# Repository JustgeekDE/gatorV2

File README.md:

# Gator
Gator started as a small project to built a set of multipurpose, breadboard friendly TTL gates. It has since morphed into the endeavour to create a complete CPU built out of only discrete NPN transistors, resistors and capacitors.  
It also serves as a test bed for a few techniques to improve the hardware development process.

(Above is a 1-bit full adder)

## Errata
- The current instruction set is missing any way to read a memory address from a register. This makes pointers, array iterations and linked list impossible or at least very hard.

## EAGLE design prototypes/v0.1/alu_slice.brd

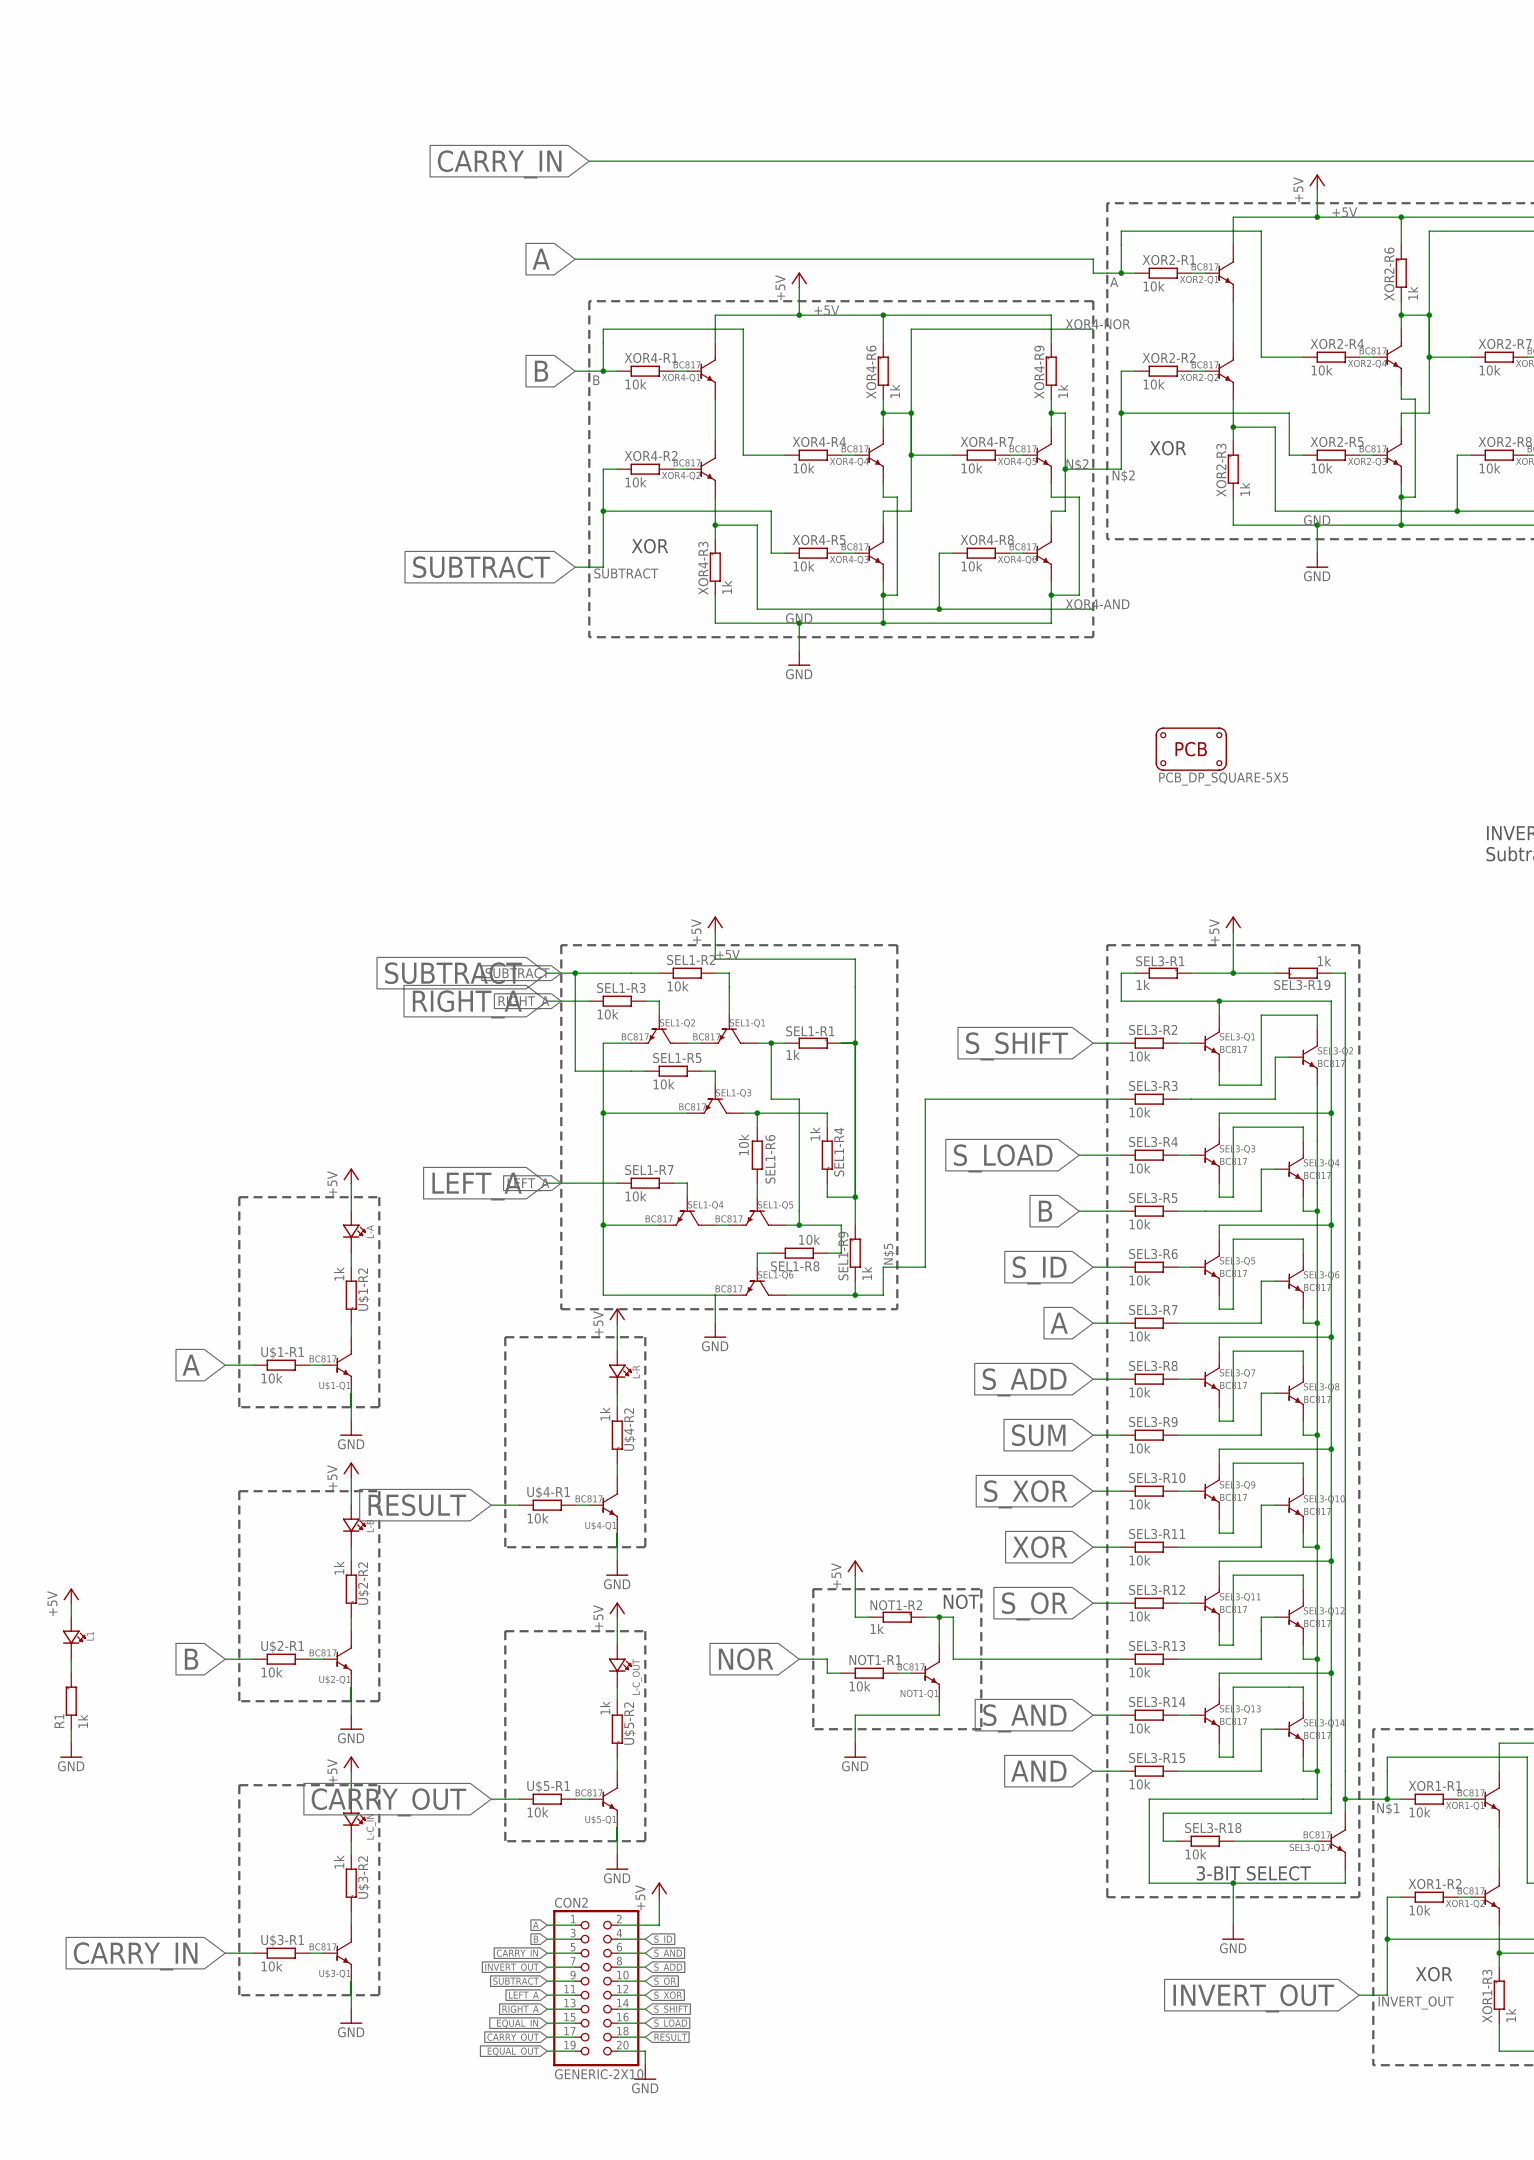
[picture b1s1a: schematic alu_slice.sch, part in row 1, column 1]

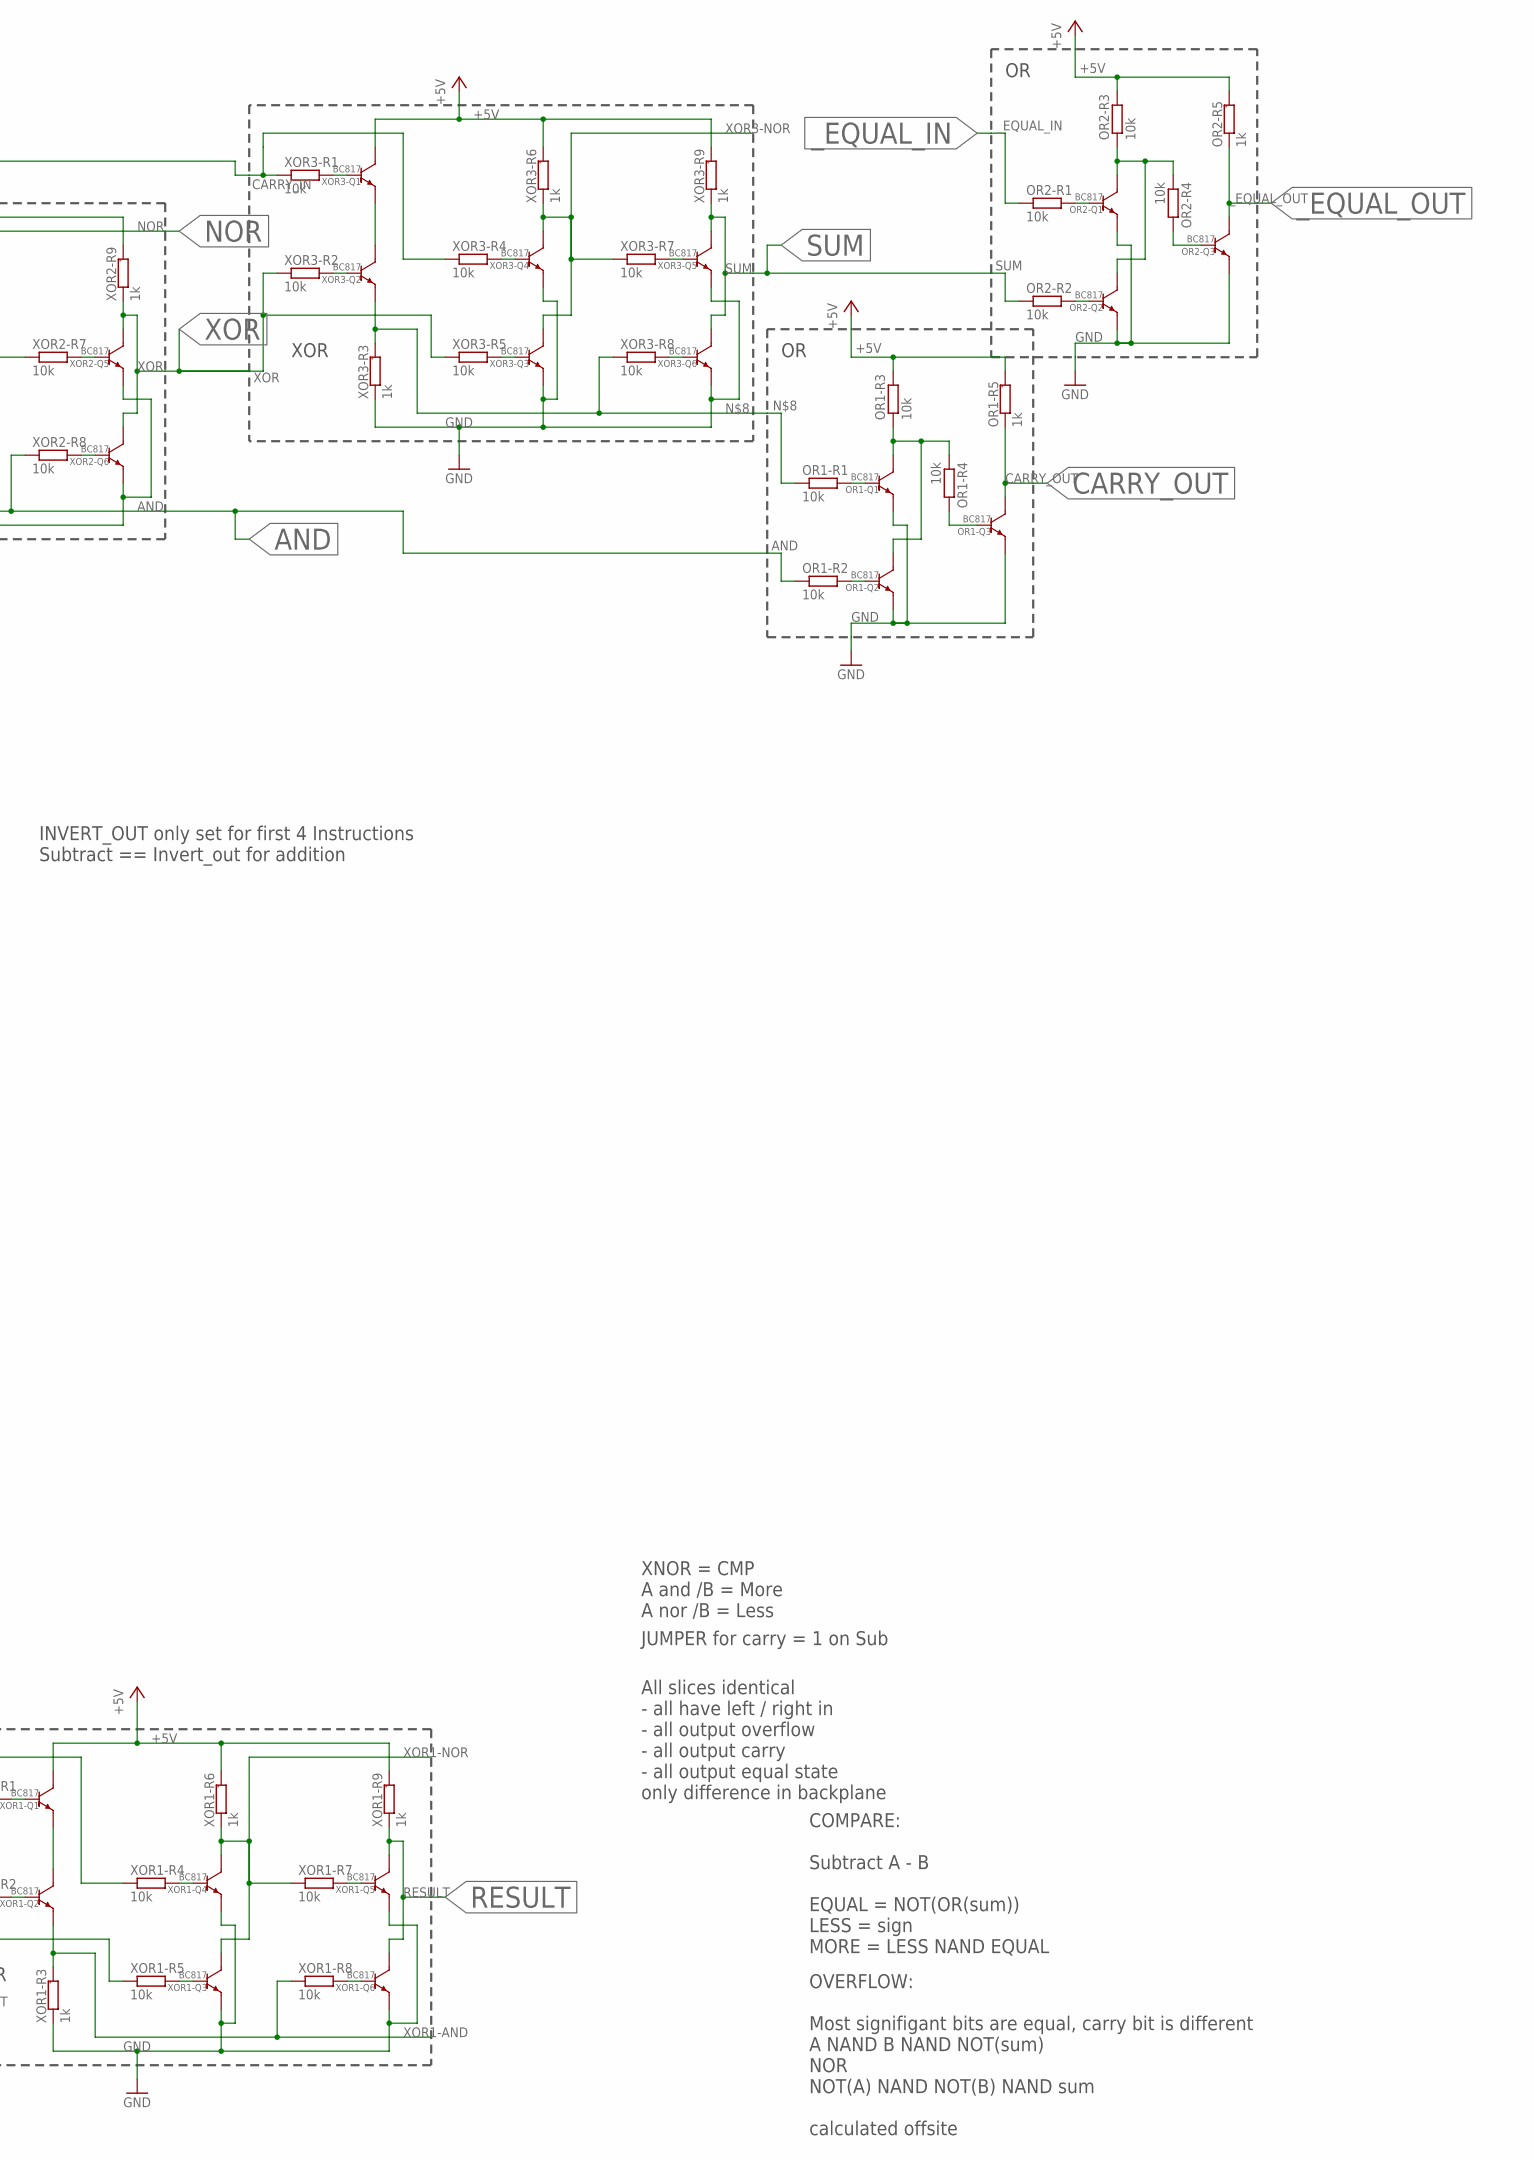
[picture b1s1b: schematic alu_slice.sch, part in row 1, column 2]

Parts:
CON2: GENERIC-2X10; PINHEADER-100MIL-2X10-EDGE
L1: LED0805; CHIPLED_0805
L-A: LED0603; CHIPLED_0603
L-B: LED0603; CHIPLED_0603
L-C_IN: LED0603; CHIPLED_0603
L-C_OUT: LED0603; CHIPLED_0603
L-R: LED0603; CHIPLED_0603
NOT1-Q1: BC817; SOT23
NOT1-R1: 10k; R0603
NOT1-R2: 1k; R0603-MARK
OR1-Q1, OR1-Q2, OR1-Q3, OR2-Q1, OR2-Q2, OR2-Q3: BC817; SOT23
OR1-R1, OR1-R2, OR1-R3, OR1-R4, OR2-R1, OR2-R2, OR2-R3, OR2-R4: 10k; R0603
OR1-R5, OR2-R5: 1k; R0603-MARK
PCB1: PCB_DP_SQUARE-5X5; DP5050_V1
R1: 1k; R0603-MARK
SEL1-Q1, SEL1-Q2, SEL1-Q3, SEL1-Q4, SEL1-Q5, SEL1-Q6, SEL3-Q1, SEL3-Q2, SEL3-Q3, SEL3-Q4, SEL3-Q5, SEL3-Q6, SEL3-Q7, SEL3-Q8, SEL3-Q9, SEL3-Q10, SEL3-Q11, SEL3-Q12, SEL3-Q13, SEL3-Q14, SEL3-Q17: BC817; SOT23
SEL1-R1, SEL1-R4, SEL1-R9, SEL3-R1, SEL3-R19: 1k; R0603-MARK
SEL1-R2, SEL1-R3, SEL1-R5, SEL1-R6, SEL1-R7, SEL1-R8, SEL3-R2, SEL3-R3, SEL3-R4, SEL3-R5, SEL3-R6, SEL3-R7, SEL3-R8, SEL3-R9, SEL3-R10, SEL3-R11, SEL3-R12, SEL3-R13, SEL3-R14, SEL3-R15, SEL3-R18: 10k; R0603
U$1-Q1, U$2-Q1, U$3-Q1, U$4-Q1, U$5-Q1: BC817; SOT23
U$1-R1, U$2-R1, U$3-R1, U$4-R1, U$5-R1: 10k; R0603
U$1-R2, U$2-R2, U$3-R2, U$4-R2, U$5-R2: 1k; R0603-MARK
XOR1-Q1, XOR1-Q2, XOR1-Q3, XOR1-Q4, XOR1-Q5, XOR1-Q6, XOR2-Q1, XOR2-Q2, XOR2-Q3, XOR2-Q4, XOR2-Q5, XOR2-Q6, XOR3-Q1, XOR3-Q2, XOR3-Q3, XOR3-Q4, XOR3-Q5, XOR3-Q6, XOR4-Q1, XOR4-Q2, XOR4-Q3, XOR4-Q4, XOR4-Q5, XOR4-Q6: BC817; SOT23
XOR1-R1, XOR1-R2, XOR1-R4, XOR1-R5, XOR1-R7, XOR1-R8, XOR2-R1, XOR2-R2, XOR2-R4, XOR2-R5, XOR2-R7, XOR2-R8, XOR3-R1, XOR3-R2, XOR3-R4, XOR3-R5, XOR3-R7, XOR3-R8, XOR4-R1, XOR4-R2, XOR4-R4, XOR4-R5, XOR4-R7, XOR4-R8: 10k; R0603
XOR1-R3, XOR1-R6, XOR1-R9, XOR2-R3, XOR2-R6, XOR2-R9, XOR3-R3, XOR3-R6, XOR3-R9, XOR4-R3, XOR4-R6, XOR4-R9: 1k; R0603-MARK

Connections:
+5V: CON2.2, L1.A, L-A.A, L-B.A, L-C_IN.A, L-C_OUT.A, L-R.A, NOT1-R2.1, OR1-R3.2, OR1-R5.2, OR2-R3.2, OR2-R5.2, SEL1-R1.2, SEL1-R4.2, SEL1-R9.2, SEL3-R1.2, SEL3-R19.2, XOR1-Q1.P$3 (COLLECTOR), XOR1-R6.2, XOR1-R9.2, XOR2-Q1.P$3 (COLLECTOR), XOR2-R6.2, XOR2-R9.2, XOR3-Q1.P$3 (COLLECTOR), XOR3-R6.2, XOR3-R9.2, XOR4-Q1.P$3 (COLLECTOR), XOR4-R6.2, XOR4-R9.2
A: CON2.1, SEL3-R7.1, U$1-R1.1, XOR2-R1.1, XOR2-R4.1
AND: OR1-R2.1, SEL3-R15.1, XOR2-Q2.P$2 (EMITTER), XOR2-R3.2, XOR2-R8.1
B: CON2.3, SEL3-R5.1, U$2-R1.1, XOR4-R1.1, XOR4-R4.1
CARRY_IN: CON2.5, U$3-R1.1, XOR3-R1.1, XOR3-R4.1
CARRY_OUT: CON2.17, OR1-Q3.P$3 (COLLECTOR), OR1-R5.1, U$5-R1.1
GND: CON2.20, NOT1-Q1.P$2 (EMITTER), OR1-Q1.P$2 (EMITTER), OR1-Q2.P$2 (EMITTER), OR1-Q3.P$2 (EMITTER), OR2-Q1.P$2 (EMITTER), OR2-Q2.P$2 (EMITTER), OR2-Q3.P$2 (EMITTER), R1.1, SEL1-Q2.P$2 (EMITTER), SEL1-Q3.P$2 (EMITTER), SEL1-Q4.P$2 (EMITTER), SEL1-Q6.P$2 (EMITTER), SEL3-Q2.P$2 (EMITTER), SEL3-Q4.P$2 (EMITTER), SEL3-Q6.P$2 (EMITTER), SEL3-Q8.P$2 (EMITTER), SEL3-Q10.P$2 (EMITTER), SEL3-Q12.P$2 (EMITTER), SEL3-Q14.P$2 (EMITTER), SEL3-Q17.P$2 (EMITTER), U$1-Q1.P$2 (EMITTER), U$2-Q1.P$2 (EMITTER), U$3-Q1.P$2 (EMITTER), U$4-Q1.P$2 (EMITTER), U$5-Q1.P$2 (EMITTER), XOR1-Q3.P$2 (EMITTER), XOR1-Q4.P$2 (EMITTER), XOR1-Q5.P$2 (EMITTER), XOR1-Q6.P$2 (EMITTER), XOR1-R3.1, XOR2-Q3.P$2 (EMITTER), XOR2-Q4.P$2 (EMITTER), XOR2-Q5.P$2 (EMITTER), XOR2-Q6.P$2 (EMITTER), XOR2-R3.1, XOR3-Q3.P$2 (EMITTER), XOR3-Q4.P$2 (EMITTER), XOR3-Q5.P$2 (EMITTER), XOR3-Q6.P$2 (EMITTER), XOR3-R3.1, XOR4-Q3.P$2 (EMITTER), XOR4-Q4.P$2 (EMITTER), XOR4-Q5.P$2 (EMITTER), XOR4-Q6.P$2 (EMITTER), XOR4-R3.1
INVERT_OUT: CON2.7, XOR1-R2.1, XOR1-R5.1
LEFT_A: CON2.11, SEL1-R7.1
unnamed: SEL3-Q17.P$3 (COLLECTOR), SEL3-R19.1, XOR1-R1.1, XOR1-R4.1
unnamed: XOR2-R2.1, XOR2-R5.1, XOR4-Q5.P$3 (COLLECTOR), XOR4-Q6.P$3 (COLLECTOR), XOR4-R9.1
unnamed: NOT1-Q1.P$3 (COLLECTOR), NOT1-R2.2, SEL3-R13.1
unnamed: SEL1-Q6.P$3 (COLLECTOR), SEL1-R9.1, SEL3-R3.1
unnamed: L1.C, R1.2
unnamed: OR1-R1.1, XOR3-Q2.P$2 (EMITTER), XOR3-R3.2, XOR3-R8.1
NOR: NOT1-R1.1, XOR2-Q3.P$3 (COLLECTOR), XOR2-Q4.P$3 (COLLECTOR), XOR2-R6.1, XOR2-R7.1
NOT1-N$14: NOT1-Q1.P$1 (BASE), NOT1-R1.2
OR1-N$7: OR1-Q1.P$1 (BASE), OR1-R1.2
OR1-N$9: OR1-Q2.P$1 (BASE), OR1-R2.2
OR1-N$10: OR1-Q3.P$1 (BASE), OR1-R4.2
OR1-N$11: OR1-Q1.P$3 (COLLECTOR), OR1-Q2.P$3 (COLLECTOR), OR1-R3.1, OR1-R4.1
OR2-N$7: OR2-Q1.P$1 (BASE), OR2-R1.2
OR2-N$9: OR2-Q2.P$1 (BASE), OR2-R2.2
OR2-N$10: OR2-Q3.P$1 (BASE), OR2-R4.2
OR2-N$11: OR2-Q1.P$3 (COLLECTOR), OR2-Q2.P$3 (COLLECTOR), OR2-R3.1, OR2-R4.1
RESULT: CON2.18, U$4-R1.1, XOR1-Q5.P$3 (COLLECTOR), XOR1-Q6.P$3 (COLLECTOR), XOR1-R9.1
RIGHT_A: CON2.13, SEL1-R3.1
SEL1-I-S2: SEL1-Q3.P$3 (COLLECTOR), SEL1-R4.1, SEL1-R6.1
SEL1-N$53: SEL1-Q1.P$1 (BASE), SEL1-R2.2
SEL1-N$55: SEL1-Q2.P$1 (BASE), SEL1-R3.2
SEL1-N$56: SEL1-Q1.P$2 (EMITTER), SEL1-Q2.P$3 (COLLECTOR)
SEL1-N$57: SEL1-Q5.P$1 (BASE), SEL1-R6.2
SEL1-N$58: SEL1-Q4.P$1 (BASE), SEL1-R7.2
SEL1-N$59: SEL1-Q4.P$3 (COLLECTOR), SEL1-Q5.P$2 (EMITTER)
SEL1-N$60: SEL1-Q6.P$1 (BASE), SEL1-R8.2
SEL1-N$62: SEL1-Q3.P$1 (BASE), SEL1-R5.2
SEL1-SEL_INT1: SEL1-Q1.P$3 (COLLECTOR), SEL1-Q5.P$3 (COLLECTOR), SEL1-R1.1, SEL1-R8.1
SEL3-N$27: SEL3-Q1.P$1 (BASE), SEL3-R2.2
SEL3-N$28: SEL3-Q2.P$1 (BASE), SEL3-R3.2
SEL3-N$29: SEL3-Q1.P$2 (EMITTER), SEL3-Q2.P$3 (COLLECTOR)
SEL3-N$32: SEL3-Q3.P$1 (BASE), SEL3-R4.2
SEL3-N$33: SEL3-Q4.P$1 (BASE), SEL3-R5.2
SEL3-N$34: SEL3-Q3.P$2 (EMITTER), SEL3-Q4.P$3 (COLLECTOR)
SEL3-N$35: SEL3-Q5.P$1 (BASE), SEL3-R6.2
SEL3-N$36: SEL3-Q6.P$1 (BASE), SEL3-R7.2
SEL3-N$37: SEL3-Q5.P$2 (EMITTER), SEL3-Q6.P$3 (COLLECTOR)
SEL3-N$38: SEL3-Q7.P$1 (BASE), SEL3-R8.2
SEL3-N$39: SEL3-Q8.P$1 (BASE), SEL3-R9.2
SEL3-N$40: SEL3-Q7.P$2 (EMITTER), SEL3-Q8.P$3 (COLLECTOR)
SEL3-N$41: SEL3-Q9.P$1 (BASE), SEL3-R10.2
SEL3-N$42: SEL3-Q10.P$1 (BASE), SEL3-R11.2
SEL3-N$43: SEL3-Q9.P$2 (EMITTER), SEL3-Q10.P$3 (COLLECTOR)
SEL3-N$44: SEL3-Q11.P$1 (BASE), SEL3-R12.2
SEL3-N$45: SEL3-Q12.P$1 (BASE), SEL3-R13.2
SEL3-N$46: SEL3-Q11.P$2 (EMITTER), SEL3-Q12.P$3 (COLLECTOR)
SEL3-N$47: SEL3-Q13.P$1 (BASE), SEL3-R14.2
SEL3-N$48: SEL3-Q14.P$1 (BASE), SEL3-R15.2
SEL3-N$49: SEL3-Q13.P$2 (EMITTER), SEL3-Q14.P$3 (COLLECTOR)
SEL3-N$54: SEL3-Q17.P$1 (BASE), SEL3-R18.2
SEL3-SEL_INT: SEL3-Q1.P$3 (COLLECTOR), SEL3-Q3.P$3 (COLLECTOR), SEL3-Q5.P$3 (COLLECTOR), SEL3-Q7.P$3 (COLLECTOR), SEL3-Q9.P$3 (COLLECTOR), SEL3-Q11.P$3 (COLLECTOR), SEL3-Q13.P$3 (COLLECTOR), SEL3-R1.1, SEL3-R18.1
SUBTRACT: CON2.9, SEL1-R2.1, SEL1-R5.1, XOR4-R2.1, XOR4-R5.1
SUM: OR2-R2.1, SEL3-R9.1, XOR3-Q5.P$3 (COLLECTOR), XOR3-Q6.P$3 (COLLECTOR), XOR3-R9.1
S_ADD: CON2.8, SEL3-R8.1
S_AND: CON2.6, SEL3-R14.1
S_ID: CON2.4, SEL3-R6.1
S_LOAD: CON2.16, SEL3-R4.1
S_OR: CON2.10, SEL3-R12.1
S_SHIFT: CON2.14, SEL3-R2.1
S_XOR: CON2.12, SEL3-R10.1
U$1-INT: L-A.C, U$1-R2.1
U$1-N$1: U$1-Q1.P$3 (COLLECTOR), U$1-R2.2
U$1-N$16: U$1-Q1.P$1 (BASE), U$1-R1.2
U$2-INT: L-B.C, U$2-R2.1
U$2-N$1: U$2-Q1.P$3 (COLLECTOR), U$2-R2.2
U$2-N$16: U$2-Q1.P$1 (BASE), U$2-R1.2
U$3-INT: L-C_IN.C, U$3-R2.1
U$3-N$1: U$3-Q1.P$3 (COLLECTOR), U$3-R2.2
U$3-N$16: U$3-Q1.P$1 (BASE), U$3-R1.2
U$4-INT: L-R.C, U$4-R2.1
U$4-N$1: U$4-Q1.P$3 (COLLECTOR), U$4-R2.2
U$4-N$16: U$4-Q1.P$1 (BASE), U$4-R1.2
U$5-INT: L-C_OUT.C, U$5-R2.1
U$5-N$1: U$5-Q1.P$3 (COLLECTOR), U$5-R2.2
U$5-N$16: U$5-Q1.P$1 (BASE), U$5-R1.2
XOR: SEL3-R11.1, XOR2-Q5.P$3 (COLLECTOR), XOR2-Q6.P$3 (COLLECTOR), XOR2-R9.1, XOR3-R2.1, XOR3-R5.1
XOR1-AND: XOR1-Q2.P$2 (EMITTER), XOR1-R3.2, XOR1-R8.1
XOR1-N$19: XOR1-Q1.P$2 (EMITTER), XOR1-Q2.P$3 (COLLECTOR)
XOR1-N$21: XOR1-Q1.P$1 (BASE), XOR1-R1.2
XOR1-N$22: XOR1-Q2.P$1 (BASE), XOR1-R2.2
XOR1-N$23: XOR1-Q3.P$1 (BASE), XOR1-R5.2
XOR1-N$24: XOR1-Q4.P$1 (BASE), XOR1-R4.2
XOR1-N$25: XOR1-Q6.P$1 (BASE), XOR1-R8.2
XOR1-N$26: XOR1-Q5.P$1 (BASE), XOR1-R7.2
XOR1-NOR: XOR1-Q3.P$3 (COLLECTOR), XOR1-Q4.P$3 (COLLECTOR), XOR1-R6.1, XOR1-R7.1
XOR2-N$19: XOR2-Q1.P$2 (EMITTER), XOR2-Q2.P$3 (COLLECTOR)
XOR2-N$21: XOR2-Q1.P$1 (BASE), XOR2-R1.2
XOR2-N$22: XOR2-Q2.P$1 (BASE), XOR2-R2.2
XOR2-N$23: XOR2-Q3.P$1 (BASE), XOR2-R5.2
XOR2-N$24: XOR2-Q4.P$1 (BASE), XOR2-R4.2
XOR2-N$25: XOR2-Q6.P$1 (BASE), XOR2-R8.2
XOR2-N$26: XOR2-Q5.P$1 (BASE), XOR2-R7.2
XOR3-N$19: XOR3-Q1.P$2 (EMITTER), XOR3-Q2.P$3 (COLLECTOR)
XOR3-N$21: XOR3-Q1.P$1 (BASE), XOR3-R1.2
XOR3-N$22: XOR3-Q2.P$1 (BASE), XOR3-R2.2
XOR3-N$23: XOR3-Q3.P$1 (BASE), XOR3-R5.2
XOR3-N$24: XOR3-Q4.P$1 (BASE), XOR3-R4.2
XOR3-N$25: XOR3-Q6.P$1 (BASE), XOR3-R8.2
XOR3-N$26: XOR3-Q5.P$1 (BASE), XOR3-R7.2
XOR3-NOR: XOR3-Q3.P$3 (COLLECTOR), XOR3-Q4.P$3 (COLLECTOR), XOR3-R6.1, XOR3-R7.1
XOR4-AND: XOR4-Q2.P$2 (EMITTER), XOR4-R3.2, XOR4-R8.1
XOR4-N$19: XOR4-Q1.P$2 (EMITTER), XOR4-Q2.P$3 (COLLECTOR)
XOR4-N$21: XOR4-Q1.P$1 (BASE), XOR4-R1.2
XOR4-N$22: XOR4-Q2.P$1 (BASE), XOR4-R2.2
XOR4-N$23: XOR4-Q3.P$1 (BASE), XOR4-R5.2
XOR4-N$24: XOR4-Q4.P$1 (BASE), XOR4-R4.2
XOR4-N$25: XOR4-Q6.P$1 (BASE), XOR4-R8.2
XOR4-N$26: XOR4-Q5.P$1 (BASE), XOR4-R7.2
XOR4-NOR: XOR4-Q3.P$3 (COLLECTOR), XOR4-Q4.P$3 (COLLECTOR), XOR4-R6.1, XOR4-R7.1
_EQUAL_IN: CON2.15, OR2-R1.1
_EQUAL_OUT: CON2.19, OR2-Q3.P$3 (COLLECTOR), OR2-R5.1

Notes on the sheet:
XNOR = CMP
A and /B = More A nor /B = Less
JUMPER for carry = 1 on Sub
All slices identical - all have left / right in - all output overflow - all output carry - all output equal state only difference in backplane
COMPARE: Subtract A - B EQUAL = NOT(OR(sum)) LESS = sign MORE = LESS NAND EQUAL
OVERFLOW: Most signifigant bits are equal, carry bit is different A NAND B NAND NOT(sum) NOR NOT(A) NAND NOT(B) NAND sum calculated offsite
INVERT_OUT only set for first 4 Instructions Subtract == Invert_out for addition
3-BIT SELECT
NOT
XOR

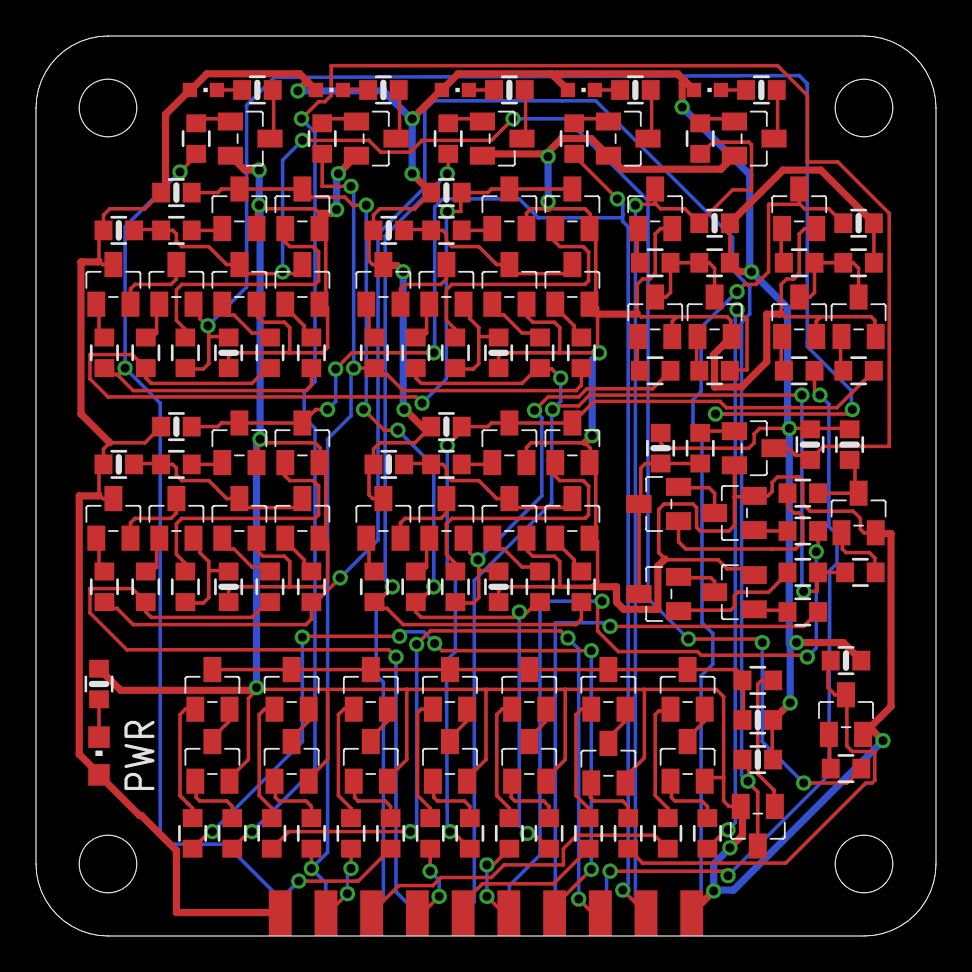
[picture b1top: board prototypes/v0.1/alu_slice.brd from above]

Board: 2 copper layers, 50.0 x 50.0 mm, 151 parts (1 on the bottom side), 120 nets.

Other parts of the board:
U$1: LOGO-JUSTGEEK-XS

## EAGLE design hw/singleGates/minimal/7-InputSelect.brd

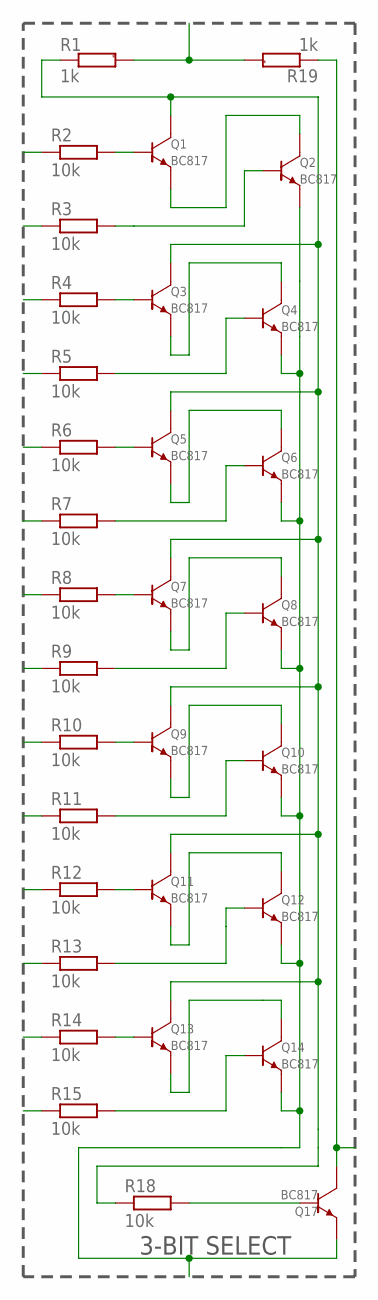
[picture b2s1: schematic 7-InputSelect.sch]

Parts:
Q1, Q2, Q3, Q4, Q5, Q6, Q7, Q8, Q9, Q10, Q11, Q12, Q13, Q14, Q17: BC817; SOT23
R1, R19: 1k; R0603-MARK
R2, R3, R4, R5, R6, R7, R8, R9, R10, R11, R12, R13, R14, R15, R18: 10k; R0603

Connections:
I1: R3.1
I2: R5.1
I3: R7.1
I4: R9.1
I5: R11.1
I6: R13.1
I7: R15.1
unnamed: Q1.P$1 (BASE), R2.2
unnamed: Q2.P$1 (BASE), R3.2
unnamed: Q1.P$2 (EMITTER), Q2.P$3 (COLLECTOR)
unnamed: Q3.P$1 (BASE), R4.2
unnamed: Q4.P$1 (BASE), R5.2
unnamed: Q3.P$2 (EMITTER), Q4.P$3 (COLLECTOR)
unnamed: Q5.P$1 (BASE), R6.2
unnamed: Q6.P$1 (BASE), R7.2
unnamed: Q5.P$2 (EMITTER), Q6.P$3 (COLLECTOR)
unnamed: Q7.P$1 (BASE), R8.2
unnamed: Q8.P$1 (BASE), R9.2
unnamed: Q7.P$2 (EMITTER), Q8.P$3 (COLLECTOR)
unnamed: Q9.P$1 (BASE), R10.2
unnamed: Q10.P$1 (BASE), R11.2
unnamed: Q9.P$2 (EMITTER), Q10.P$3 (COLLECTOR)
unnamed: Q11.P$1 (BASE), R12.2
unnamed: Q12.P$1 (BASE), R13.2
unnamed: Q11.P$2 (EMITTER), Q12.P$3 (COLLECTOR)
unnamed: Q13.P$1 (BASE), R14.2
unnamed: Q14.P$1 (BASE), R15.2
unnamed: Q13.P$2 (EMITTER), Q14.P$3 (COLLECTOR)
unnamed: Q17.P$1 (BASE), R18.2
OUT: Q17.P$3 (COLLECTOR), R19.1
S1: R2.1
S2: R4.1
S3: R6.1
S4: R8.1
S5: R10.1
S6: R12.1
S7: R14.1
SEL_INT: Q1.P$3 (COLLECTOR), Q3.P$3 (COLLECTOR), Q5.P$3 (COLLECTOR), Q7.P$3 (COLLECTOR), Q9.P$3 (COLLECTOR), Q11.P$3 (COLLECTOR), Q13.P$3 (COLLECTOR), R1.1, R18.1
_VN: Q2.P$2 (EMITTER), Q4.P$2 (EMITTER), Q6.P$2 (EMITTER), Q8.P$2 (EMITTER), Q10.P$2 (EMITTER), Q12.P$2 (EMITTER), Q14.P$2 (EMITTER), Q17.P$2 (EMITTER)
_VP: R1.2, R19.2

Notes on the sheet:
3-BIT SELECT

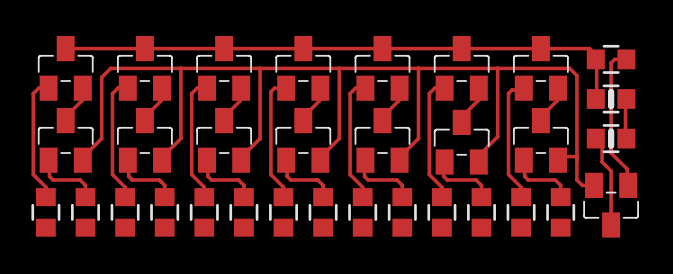
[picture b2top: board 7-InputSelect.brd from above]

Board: 2 copper layers, 32 parts (0 on the bottom side), 26 nets.

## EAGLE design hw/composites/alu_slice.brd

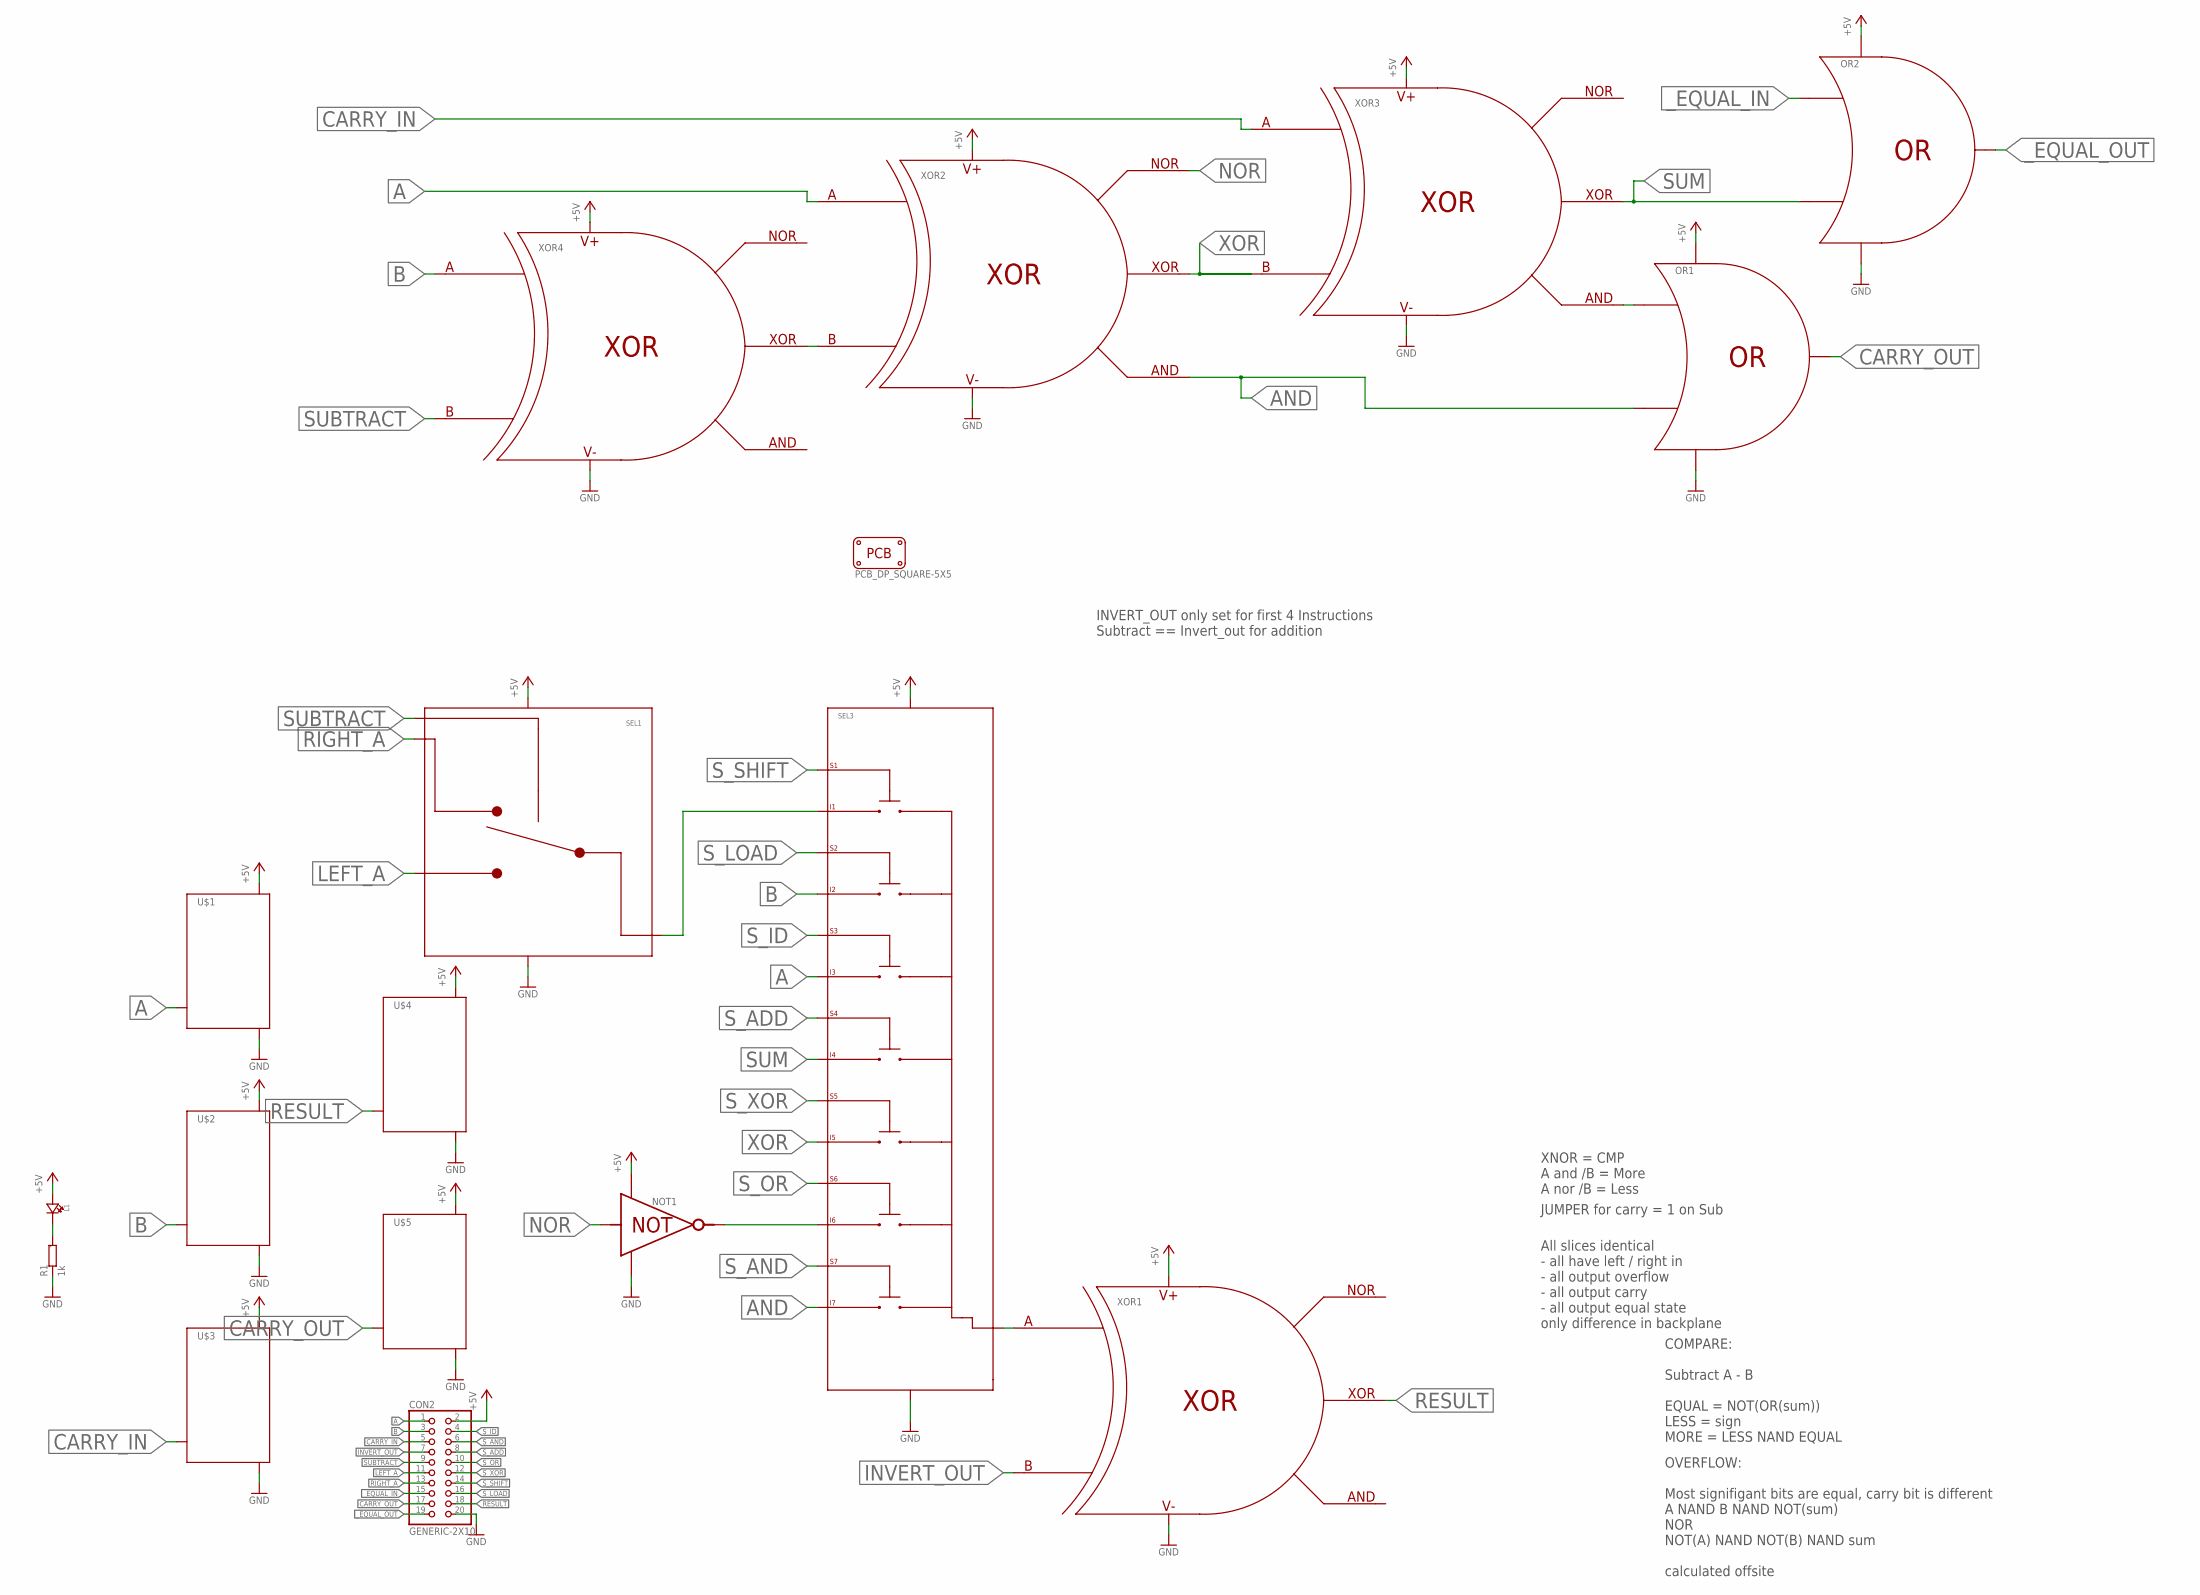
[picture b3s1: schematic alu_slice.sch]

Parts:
CON2: GENERIC-2X10; PINHEADER-100MIL-2X10-EDGE
L1: LED0805; CHIPLED_0805
NOT1: NOTVERTICAL; NOT-VERTICAL
OR1, OR2: OR
PCB1: PCB_DP_SQUARE-5X5; DP5050_V1
R1: 1k; R0603-MARK
SEL1: 1_BIT_SELECT; SELECTOR-2-LANE-NOMUX
SEL3: 7_VAL_SELECT; SELECTOR-7_BIT-NOMUX
U$1, U$2, U$3, U$4, U$5: LEDDRIVER
XOR1, XOR2, XOR3, XOR4: XOR

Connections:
+5V: CON2.2, L1.A, NOT1._VP, OR1._VP, OR2._VP, SEL1._VP, SEL3._VP, U$1._VP, U$2._VP, U$3._VP, U$4._VP, U$5._VP, XOR1._VP, XOR2._VP, XOR3._VP, XOR4._VP
A: CON2.1, SEL3.I3, U$1.A, XOR2.A
AND: OR1.B, SEL3.I7, XOR2.AND
B: CON2.3, SEL3.I2, U$2.A, XOR4.A
CARRY_IN: CON2.5, U$3.A, XOR3.A
CARRY_OUT: CON2.17, OR1.OR, U$5.A
GND: CON2.20, NOT1._VN, OR1._VN, OR2._VN, R1.1, SEL1._VN, SEL3._VN, U$1._VN, U$2._VN, U$3._VN, U$4._VN, U$5._VN, XOR1._VN, XOR2._VN, XOR3._VN, XOR4._VN
INVERT_OUT: CON2.7, XOR1.B
LEFT_A: CON2.11, SEL1.B
unnamed: SEL3.OUT, XOR1.A
unnamed: XOR2.B, XOR4.XOR
unnamed: NOT1.NOT, SEL3.I6
unnamed: SEL1.OUT, SEL3.I1
unnamed: L1.C, R1.2
unnamed: OR1.A, XOR3.AND
NOR: NOT1.A, XOR2.NOR
RESULT: CON2.18, U$4.A, XOR1.XOR
RIGHT_A: CON2.13, SEL1.A
SUBTRACT: CON2.9, SEL1.SEL, XOR4.B
SUM: OR2.B, SEL3.I4, XOR3.XOR
S_ADD: CON2.8, SEL3.S4
S_AND: CON2.6, SEL3.S7
S_ID: CON2.4, SEL3.S3
S_LOAD: CON2.16, SEL3.S2
S_OR: CON2.10, SEL3.S6
S_SHIFT: CON2.14, SEL3.S1
S_XOR: CON2.12, SEL3.S5
XOR: SEL3.I5, XOR2.XOR, XOR3.B
_EQUAL_IN: CON2.15, OR2.A
_EQUAL_OUT: CON2.19, OR2.OR

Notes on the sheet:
XNOR = CMP
A and /B = More A nor /B = Less
JUMPER for carry = 1 on Sub
All slices identical - all have left / right in - all output overflow - all output carry - all output equal state only difference in backplane
COMPARE: Subtract A - B EQUAL = NOT(OR(sum)) LESS = sign MORE = LESS NAND EQUAL
OVERFLOW: Most signifigant bits are equal, carry bit is different A NAND B NAND NOT(sum) NOR NOT(A) NAND NOT(B) NAND sum calculated offsite
INVERT_OUT only set for first 4 Instructions Subtract == Invert_out for addition

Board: 2 copper layers, 18 parts (0 on the bottom side), 30 nets, no tracks yet.

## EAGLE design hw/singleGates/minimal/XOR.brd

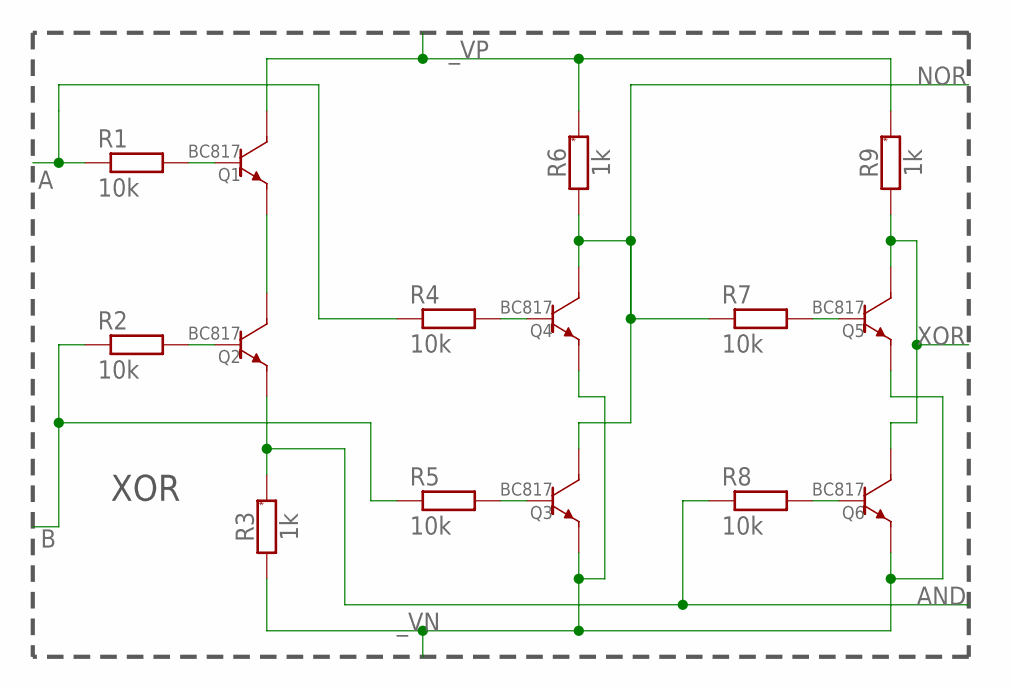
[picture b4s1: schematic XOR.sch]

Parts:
Q1, Q2, Q3, Q4, Q5, Q6: BC817; SOT23
R1, R2, R4, R5, R7, R8: 10k; R0603
R3, R6, R9: 1k; R0603-MARK

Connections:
A: R1.1, R4.1
AND: Q2.P$2 (EMITTER), R3.2, R8.1
B: R2.1, R5.1
unnamed: Q1.P$2 (EMITTER), Q2.P$3 (COLLECTOR)
unnamed: Q1.P$1 (BASE), R1.2
unnamed: Q2.P$1 (BASE), R2.2
unnamed: Q3.P$1 (BASE), R5.2
unnamed: Q4.P$1 (BASE), R4.2
unnamed: Q6.P$1 (BASE), R8.2
unnamed: Q5.P$1 (BASE), R7.2
NOR: Q3.P$3 (COLLECTOR), Q4.P$3 (COLLECTOR), R6.1, R7.1
XOR: Q5.P$3 (COLLECTOR), Q6.P$3 (COLLECTOR), R9.1
_VN: Q3.P$2 (EMITTER), Q4.P$2 (EMITTER), Q5.P$2 (EMITTER), Q6.P$2 (EMITTER), R3.1
_VP: Q1.P$3 (COLLECTOR), R6.2, R9.2

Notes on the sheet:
XOR

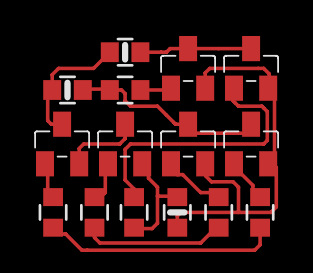
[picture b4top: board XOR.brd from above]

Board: 2 copper layers, 15 parts (0 on the bottom side), 14 nets.

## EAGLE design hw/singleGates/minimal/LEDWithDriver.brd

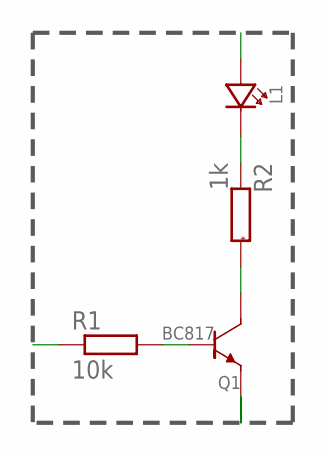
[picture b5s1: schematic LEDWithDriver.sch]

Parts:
L1: LED0603; CHIPLED_0603
Q1: BC817; SOT23
R1: 10k; R0603
R2: 1k; R0603-MARK

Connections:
A: R1.1
INT: L1.C, R2.1
unnamed: Q1.P$3 (COLLECTOR), R2.2
unnamed: Q1.P$1 (BASE), R1.2
_VN: Q1.P$2 (EMITTER)
_VP: L1.A

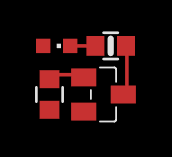
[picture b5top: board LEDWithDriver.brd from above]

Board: 2 copper layers, 4 parts (0 on the bottom side), 3 nets.

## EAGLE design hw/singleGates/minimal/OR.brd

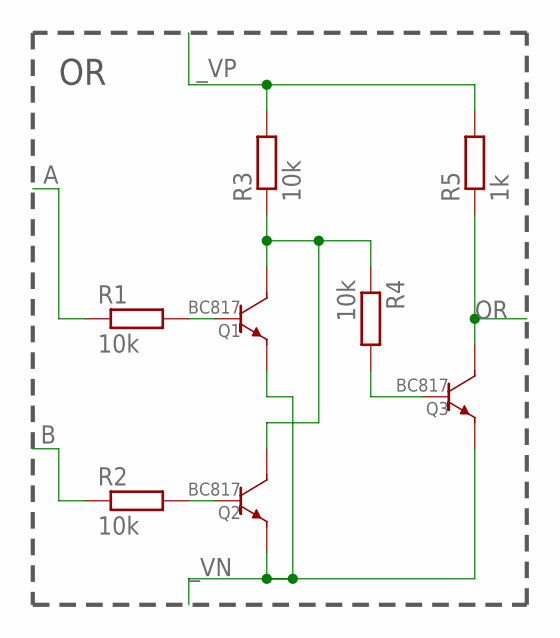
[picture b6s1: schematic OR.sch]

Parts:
Q1, Q2, Q3: BC817; SOT23
R1, R2, R3, R4: 10k; R0603
R5: 1k; R0603

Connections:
A: R1.1
B: R2.1
unnamed: Q1.P$1 (BASE), R1.2
unnamed: Q2.P$1 (BASE), R2.2
unnamed: Q3.P$1 (BASE), R4.2
unnamed: Q1.P$3 (COLLECTOR), Q2.P$3 (COLLECTOR), R3.1, R4.1
OR: Q3.P$3 (COLLECTOR), R5.1
_VN: Q1.P$2 (EMITTER), Q2.P$2 (EMITTER), Q3.P$2 (EMITTER)
_VP: R3.2, R5.2

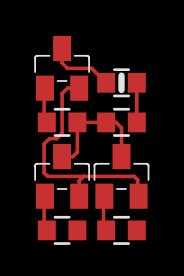
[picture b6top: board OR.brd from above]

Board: 2 copper layers, 8 parts (0 on the bottom side), 7 nets.
